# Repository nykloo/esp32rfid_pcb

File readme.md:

### ESP32 rfid circuit 
## 125khz rfid reader/writer for EM4x chips
### Works for kyber crystals
## Firmware
https://github.com/nykloo/ESP32RFID-Firmware
## Control App
https://github.com/nykloo/ESP32RFID-App
## IMPORTANT NOTES
+ C_RESA1, C_RESB1,C_DV1, C_DV2 should be fairly close to their intended values (ie use capicitors with a tolerance of less than 5%) Alternatively the optional capacitors can be used to more  tune the resonate frequency of the antenna circuit. 
+ The PCB coil antenna is designed to printed on a pcb with thickness of 1mm and outer copper weight of 1 oz. I have been ordering these from jlc pcb.

## Schematic

## PCB

## Assembly

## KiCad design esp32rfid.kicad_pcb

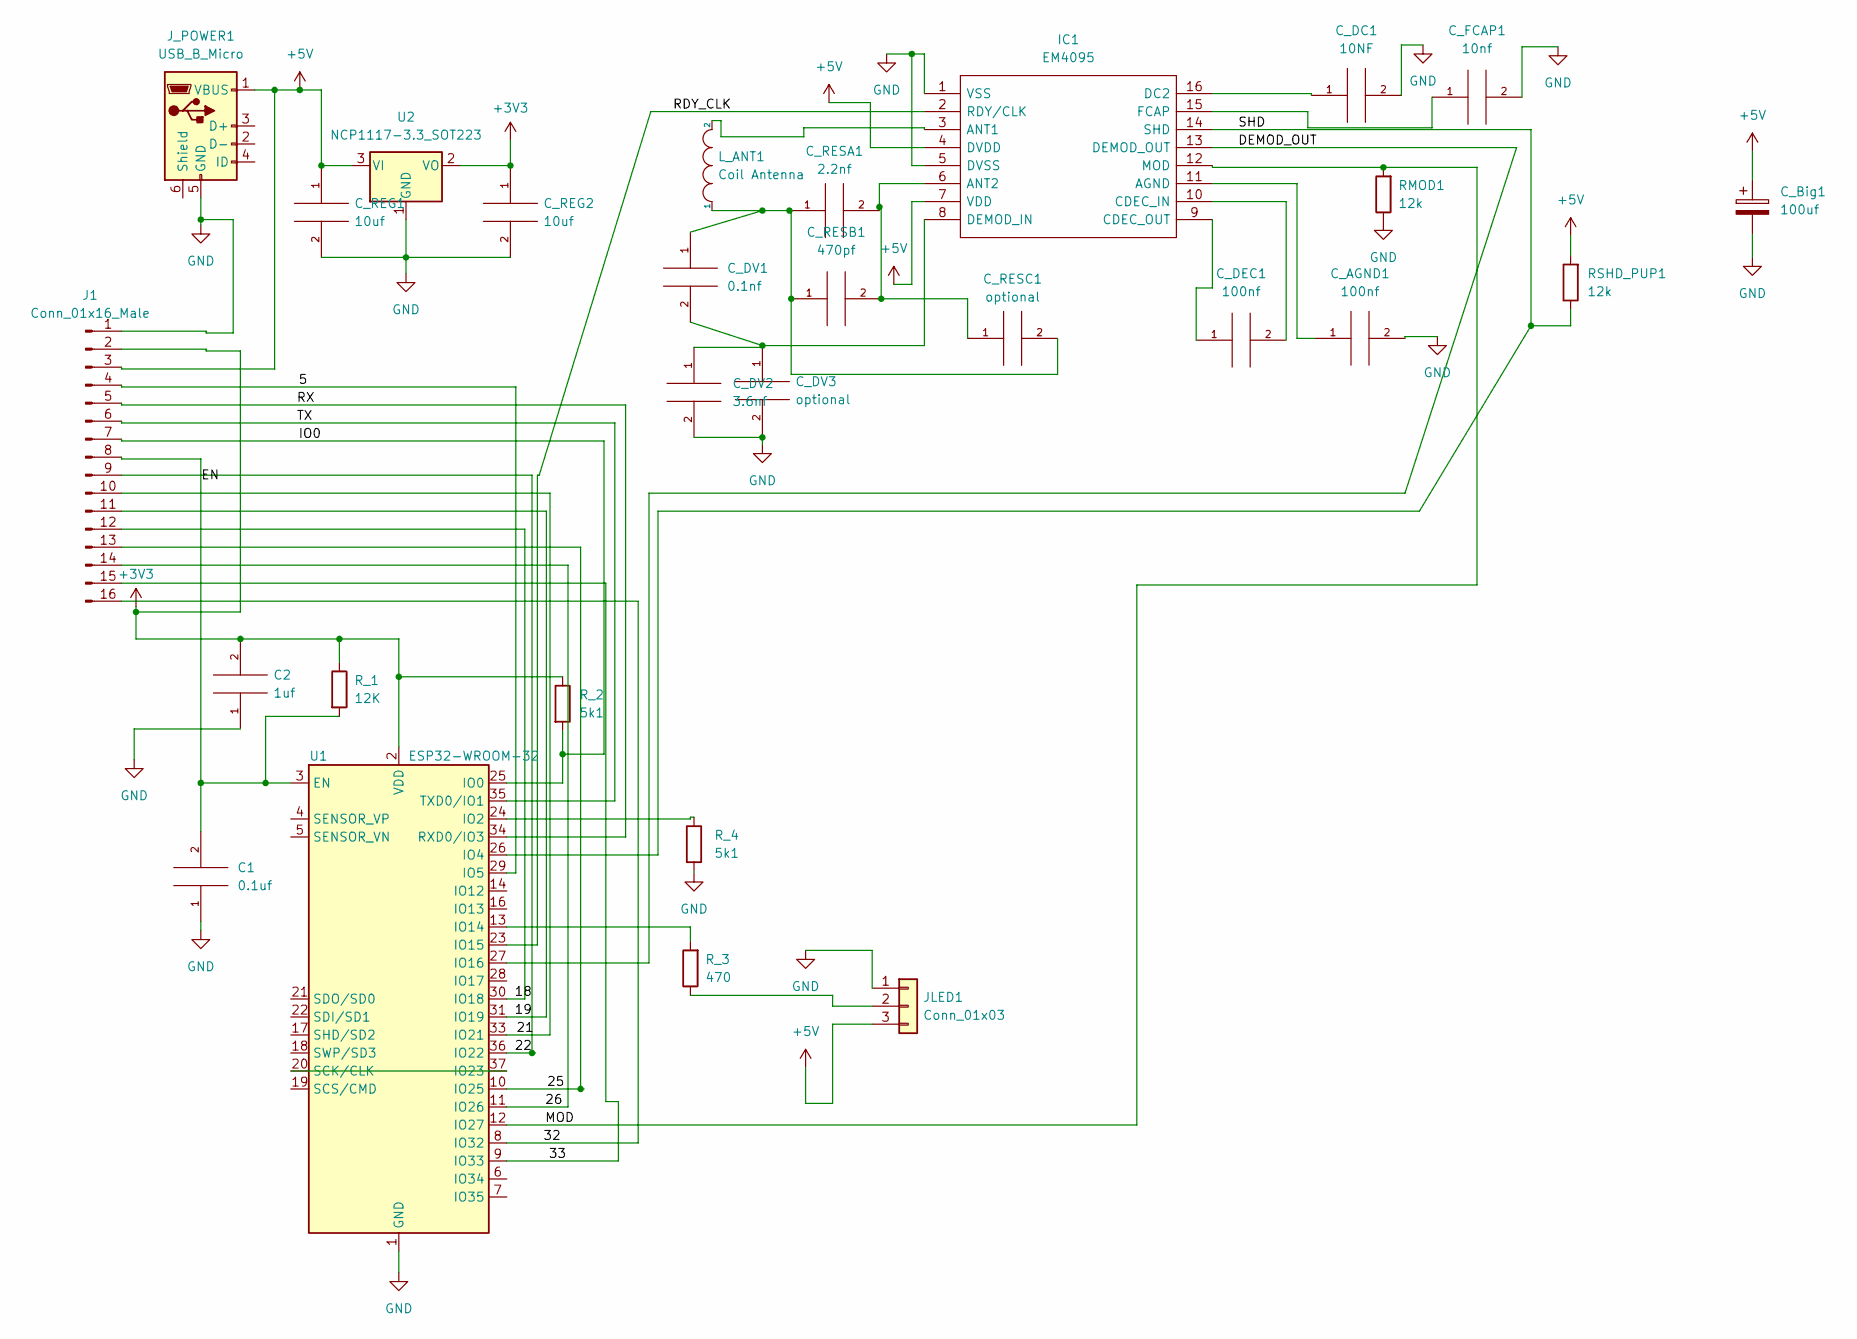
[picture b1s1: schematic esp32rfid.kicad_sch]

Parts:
C1: 0.1uf; C_0805_2012Metric_Pad1.18x1.45mm_HandSolder
C2: 1uf; C_0805_2012Metric_Pad1.18x1.45mm_HandSolder
C_AGND1: 100nf; C_0805_2012Metric_Pad1.18x1.45mm_HandSolder
C_Big1: 100uf; CP_Elec_8x10.5
C_DC1: 10NF; C_0805_2012Metric_Pad1.18x1.45mm_HandSolder
C_DEC1: 100nf; C_0805_2012Metric_Pad1.18x1.45mm_HandSolder
C_DV1: 0.1nf; C_0805_2012Metric_Pad1.18x1.45mm_HandSolder
C_DV2: 3.6nf; C_0805_2012Metric_Pad1.18x1.45mm_HandSolder
C_DV3: optional; C_0805_2012Metric_Pad1.18x1.45mm_HandSolder
C_FCAP1: 10nf; C_0805_2012Metric_Pad1.18x1.45mm_HandSolder
C_REG1, C_REG2: 10uf; C_0805_2012Metric_Pad1.18x1.45mm_HandSolder
C_RESA1: 2.2nf; C_0805_2012Metric_Pad1.18x1.45mm_HandSolder
C_RESB1: 470pf; C_0805_2012Metric_Pad1.18x1.45mm_HandSolder
C_RESC1: optional; C_0805_2012Metric_Pad1.18x1.45mm_HandSolder
IC1: EM4095; SOIC127P602X173-16N; Manufacturer_Part_Number EM4095
J1: Conn_01x16_Male; PinHeader_1x16_P2.54mm_Vertical
JLED1: Conn_01x03; FanPinHeader_1x03_P2.54mm_Vertical
J_POWER1: USB_B_Micro; USB_Micro-B_Molex_47346-0001
L_ANT1: Coil Antenna; 60_turn_square_inductor_corrected
RMOD1: 12k; R_0805_2012Metric_Pad1.20x1.40mm_HandSolder
RSHD_PUP1: 12k; R_0805_2012Metric_Pad1.20x1.40mm_HandSolder
R_1: 12K; R_0805_2012Metric_Pad1.20x1.40mm_HandSolder
R_2, R_4: 5k1; R_0805_2012Metric_Pad1.20x1.40mm_HandSolder
R_3: 470; R_0805_2012Metric_Pad1.20x1.40mm_HandSolder
U1: ESP32-WROOM-32
U2: NCP1117-3.3_SOT223; SOT-223-3_TabPin2

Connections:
+3V3: C2.2, C_REG2.1, J1.2, R_1.1, R_2.1, U1.2 (VDD), U2.2 (VO)
+5V: C_Big1.1, C_REG1.1, IC1.4 (DVDD), IC1.7 (VDD), J1.3, JLED1.3, J_POWER1.1 (VBUS), RSHD_PUP1.2, U2.3 (VI)
/5: J1.4, U1.29 (IO5)
/18: J1.12, U1.30 (IO18)
/19: J1.11, U1.31 (IO19)
/21: J1.10, U1.33 (IO21)
/22: J1.9, U1.36 (IO22)
/25: J1.13, U1.10 (IO25)
/26: J1.14, U1.11 (IO26)
/32: J1.16, U1.8 (IO32)
/33: J1.15, U1.9 (IO33)
/DEMOD_OUT: IC1.13 (DEMOD_OUT), U1.27 (IO16)
/EN: C1.2, J1.8, R_1.2, U1.3 (EN)
/IO0: J1.7, R_2.2, U1.25 (IO0)
/MOD: IC1.12 (MOD), RMOD1.2, U1.12 (IO27)
/RDY_CLK: IC1.2 (RDY/CLK), U1.23 (IO15)
/RX: J1.5, U1.34 (RXD0/IO3)
/SHD: IC1.14 (SHD), RSHD_PUP1.1, U1.26 (IO4)
/TX: J1.6, U1.35 (TXD0/IO1)
GND: C1.1, C2.1, C_AGND1.2, C_Big1.2, C_DC1.2, C_DV2.2, C_DV3.2, C_FCAP1.2, C_REG1.2, C_REG2.2, IC1.1 (VSS), IC1.5 (DVSS), J1.1, JLED1.1, J_POWER1.5 (GND), RMOD1.1, R_4.2, U1.1 (GND), U1.15 (GND), U1.38 (GND), U1.39 (GND), U2.1 (GND)
unnamed: C_AGND1.1, IC1.11 (AGND)
unnamed: C_DC1.1, IC1.16 (DC2)
unnamed: C_DEC1.1, IC1.9 (CDEC_OUT)
unnamed: C_DEC1.2, IC1.10 (CDEC_IN)
unnamed: C_DV1.1, C_RESA1.1, C_RESB1.1, C_RESC1.2, L_ANT1.1
unnamed: C_DV1.2, C_DV2.1, C_DV3.1, IC1.8 (DEMOD_IN)
unnamed: C_FCAP1.1, IC1.15 (FCAP)
unnamed: C_RESA1.2, C_RESB1.2, C_RESC1.1, IC1.6 (ANT2)
unnamed: IC1.3 (ANT1), L_ANT1.2
unnamed: JLED1.2, R_3.1
unnamed: R_3.2, U1.13 (IO14)
unnamed: R_4.1, U1.24 (IO2)
unnamed: U1.20 (SCK/CLK), U1.37 (IO23)

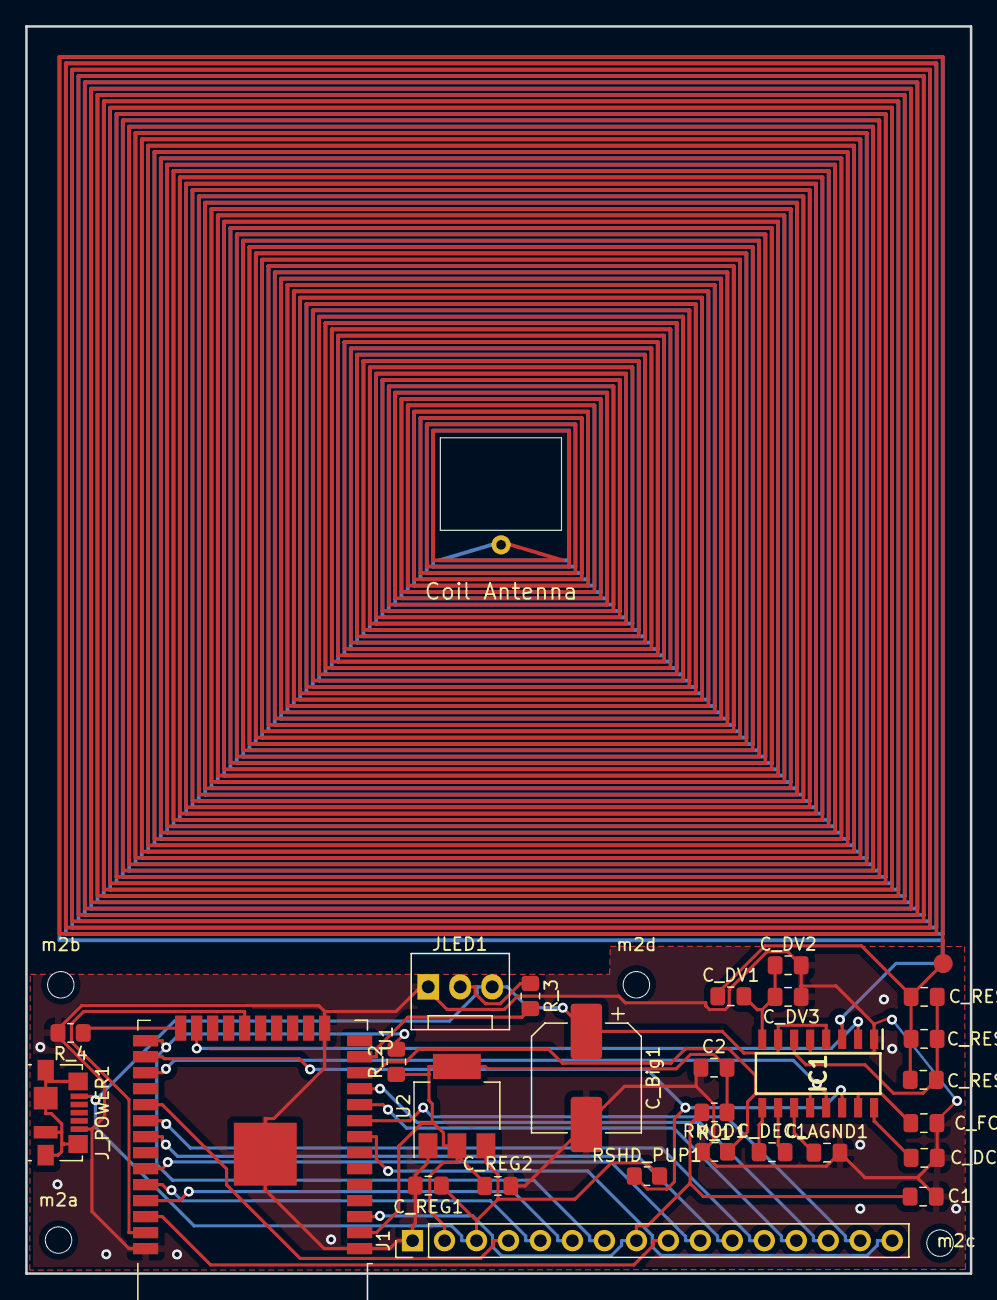
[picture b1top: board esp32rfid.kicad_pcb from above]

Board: 2 copper layers, 75.0 x 99.1 mm, 32 parts (0 on the bottom side), 33 nets.

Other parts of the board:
m2a, m2b, m2c, m2d: MountingHole_2.1mm

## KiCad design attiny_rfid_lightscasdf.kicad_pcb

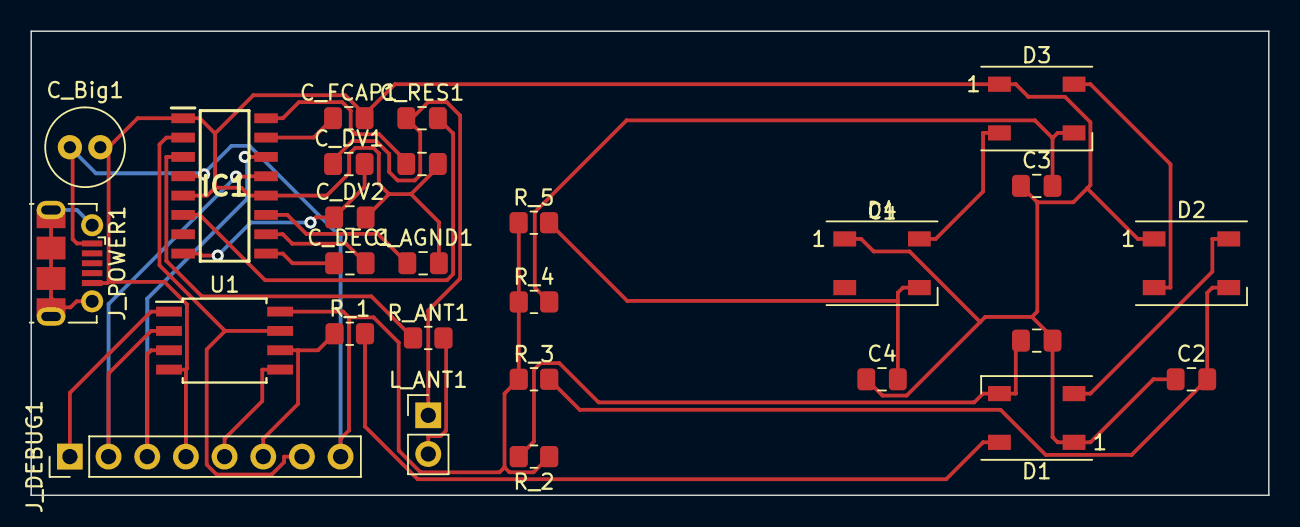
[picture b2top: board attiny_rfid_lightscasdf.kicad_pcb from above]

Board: 2 copper layers, 81.3 x 30.5 mm, 27 parts (0 on the bottom side), 26 nets.

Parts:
C1, C2, C3: 0.1uf; C_0805_2012Metric_Pad1.18x1.45mm_HandSolder
C4: 0.1uF; C_0805_2012Metric_Pad1.18x1.45mm_HandSolder
C_AGND1: C; C_0805_2012Metric_Pad1.18x1.45mm_HandSolder
C_Big1: 10uf; C_Radial_D5.0mm_H11.0mm_P2.00mm
C_DC2: C; C_0805_2012Metric_Pad1.18x1.45mm_HandSolder
C_DEC1: C; C_0805_2012Metric_Pad1.18x1.45mm_HandSolder
C_DV1, C_DV2: C; C_0805_2012Metric_Pad1.18x1.45mm_HandSolder
C_FCAP1: C; C_0805_2012Metric_Pad1.18x1.45mm_HandSolder
C_RES1: C; C_0805_2012Metric_Pad1.18x1.45mm_HandSolder
D1, D2, D3, D4: WS2812B; LED_WS2812B_PLCC4_5.0x5.0mm_P3.2mm
IC1: EM4095; SOIC127P602X173-16N
J_DEBUG1: Conn_01x08_Male; PinHeader_1x08_P2.54mm_Vertical
J_POWER1: USB_B_Micro; USB_Micro-B_Molex-105017-0001
L_ANT1: Coil Antenna; PinHeader_1x02_P2.54mm_Vertical
R_1: 490; R_0805_2012Metric_Pad1.20x1.40mm_HandSolder
R_2, R_3, R_4, R_5: 150; R_0805_2012Metric_Pad1.20x1.40mm_HandSolder
R_ANT1: 10; R_0805_2012Metric_Pad1.20x1.40mm_HandSolder
U1: ATtiny85-20S; SOIC-8W_5.3x5.3mm_P1.27mm

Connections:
+5V: C_Big1.1, IC1.4 (DVDD), J_DEBUG1.8, J_POWER1.1 (VBUS), R_2.1, R_3.1, R_4.1, R_5.1, U1.8 (VCC)
GND: C1.1, C2.1, C3.1, C4.1, C_AGND1.2, C_Big1.2, C_DC2.2, C_DV2.2, C_FCAP1.2, D1.1 (VDD), D2.1 (VDD), D3.1 (VDD), D4.1 (VDD), IC1.1 (VSS), IC1.5 (DVSS), IC1.12 (MOD), J_DEBUG1.4, J_POWER1.5 (GND), U1.4 (GND)
unnamed: C_AGND1.1, IC1.11 (AGND)
unnamed: C_DC2.1, IC1.16 (DC2)
unnamed: C_DEC1.1, IC1.9 (CDEC_OUT)
unnamed: C_DEC1.2, IC1.10 (CDEC_IN)
unnamed: C_DV1.1, C_RES1.1, L_ANT1.1
unnamed: C_DV1.2, C_DV2.1, IC1.8 (DEMOD_IN)
unnamed: C_FCAP1.1, IC1.15 (FCAP)
unnamed: C_RES1.2, IC1.6 (ANT2)
unnamed: D1.2 (DOUT), D2.4 (DIN)
unnamed: D2.2 (DOUT), D3.4 (DIN)
unnamed: D3.2 (DOUT), D4.4 (DIN)
unnamed: J_DEBUG1.1, U1.1 (~RESET/PB5)
unnamed: IC1.13 (DEMOD_OUT), J_DEBUG1.2, U1.2 (XTAL1/PB3)
unnamed: IC1.14 (SHD), J_DEBUG1.3, U1.3 (XTAL2/PB4)
unnamed: J_DEBUG1.5, U1.5 (AREF/PB0)
unnamed: IC1.2 (RDY/CLK), J_DEBUG1.7, U1.7 (PB2)
unnamed: J_DEBUG1.6, R_1.1, U1.6 (PB1)
unnamed: D1.4 (DIN), R_1.2
unnamed: C1.2, D1.3 (VSS), R_2.2
unnamed: C2.2, D2.3 (VSS), R_3.2
unnamed: C3.2, D3.3 (VSS), R_4.2
unnamed: C4.2, D4.3 (VSS), R_5.2
unnamed: IC1.3 (ANT1), R_ANT1.1
unnamed: L_ANT1.2, R_ANT1.2

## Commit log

2022-09-13 created schematic
2022-10-21 va plus alittle
2022-10-21 Update fix antenna direction and missing shd trace
2022-11-12 updated values to match place values
2023-07-18 Clean up and prep for release
